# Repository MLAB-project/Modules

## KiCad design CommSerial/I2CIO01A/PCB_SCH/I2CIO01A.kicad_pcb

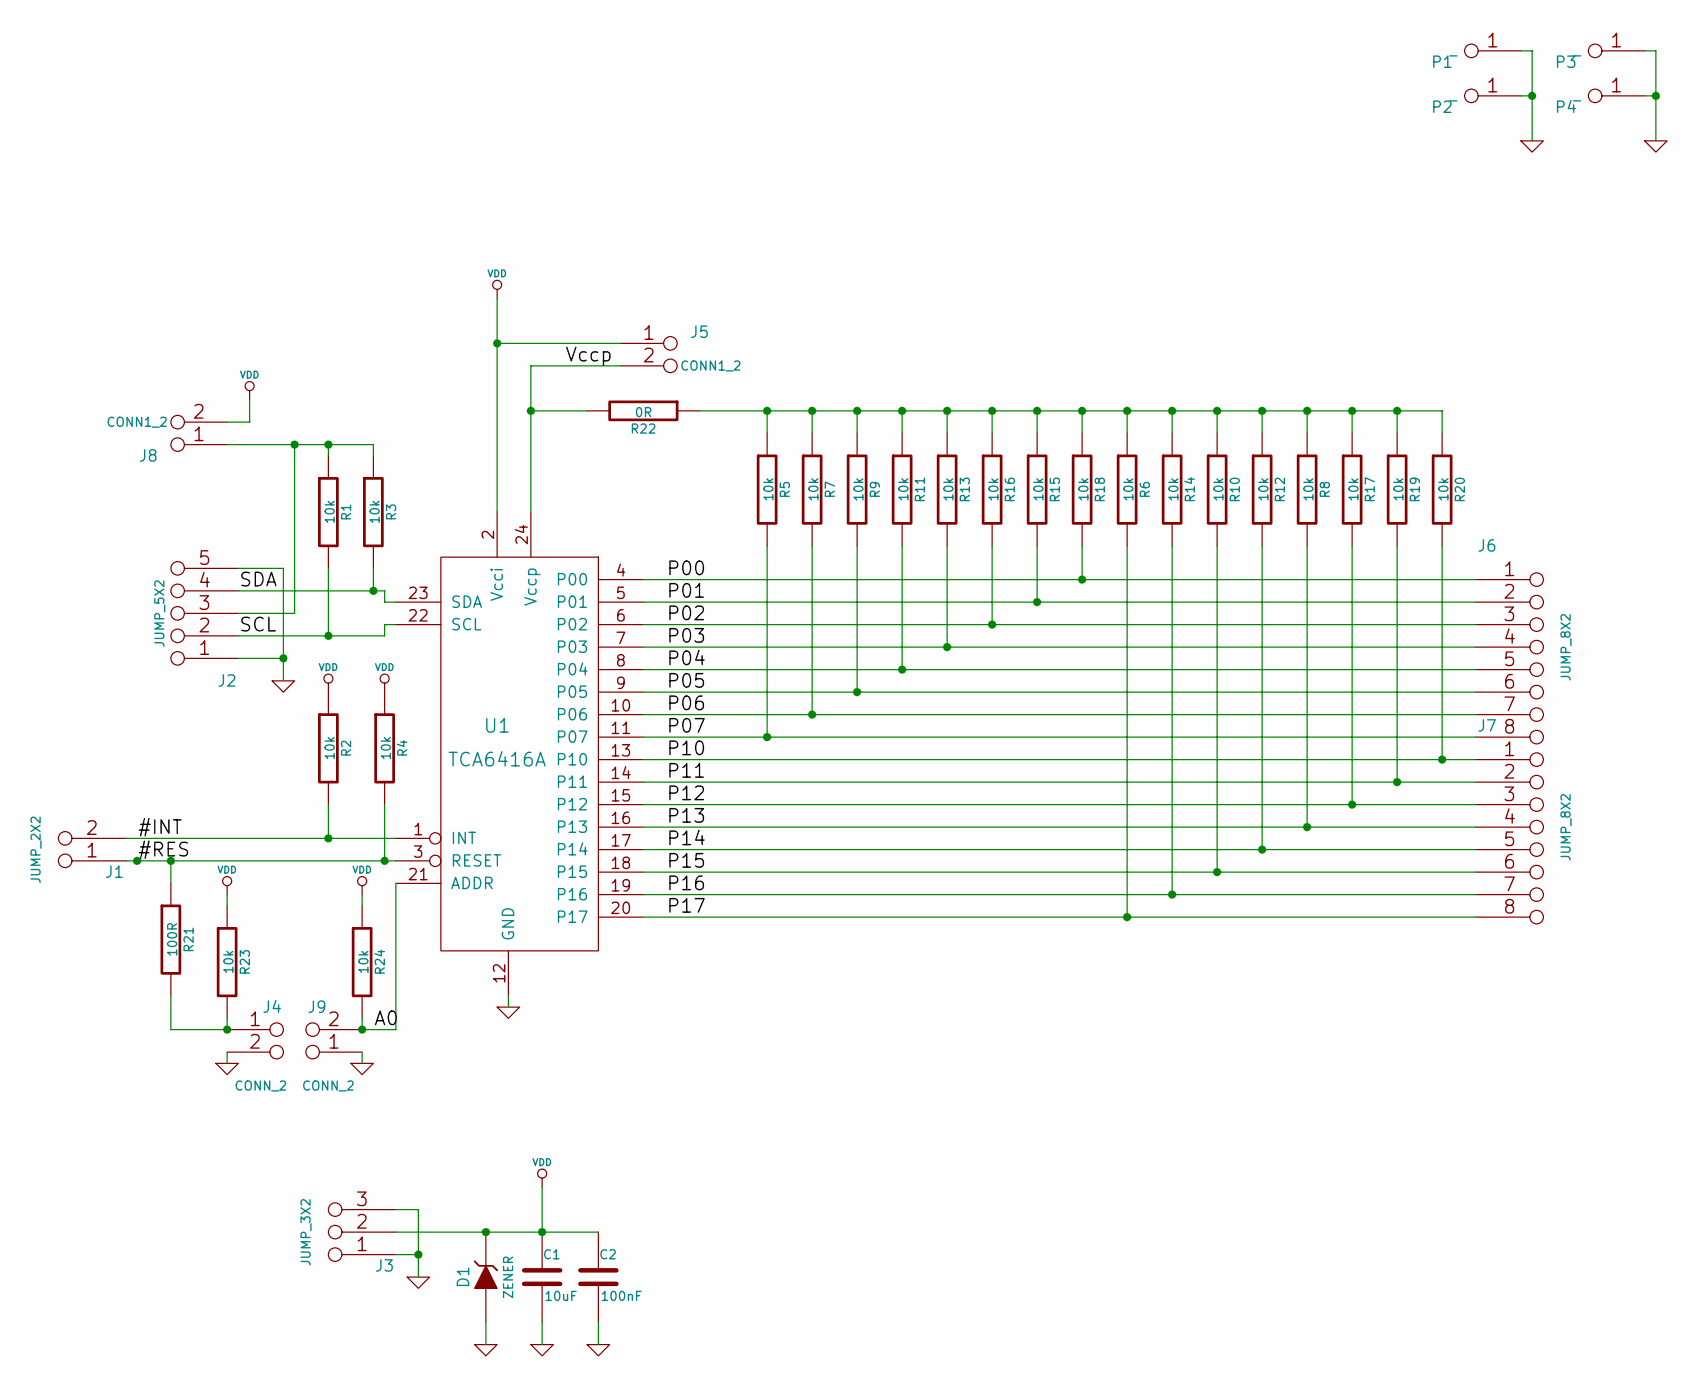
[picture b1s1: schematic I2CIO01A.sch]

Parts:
C1: 10uF; SMD-0805
C2: 100nF; SMD-0805
D1: ZENER; Diode-MiniMELF_Standard
J1: JUMP_2X2; Pin_Header_Straight_2x02
J2: JUMP_5X2; Pin_Header_Straight_2x05
J3: JUMP_3X2; Pin_Header_Straight_2x03
J4, J9: CONN_2; Pin_Header_Straight_1x02
J5, J8: CONN1_2; Pin_Header_Straight_1x02
J6, J7: JUMP_8X2; Pin_Header_Straight_2x08
P1, P2, P3, P4: _; MountingHole_3mm
R1, R2, R3, R4, R5, R6, R7, R8, R9, R10, R11, R12, R13, R14, R15, R16, R17, R18, R19, R20, R23, R24: 10k; SMD-0805
R21: 100R; SMD-0805
R22: 0R; SMD-0805
U1: TCA6416A; TSSOP-28

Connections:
/#INT: J1.2 (1), J1.3, R2.2, U1.1 (INT)
/#RES: J1.1, J1.4, R4.2, R21.1, U1.3 (RESET)
/A0: J9.2 (PM), R24.2, U1.21 (ADDR)
/P00: J6.1, J6.16, R18.2, U1.4 (P00)
/P01: J6.2, J6.15, R15.2, U1.5 (P01)
/P02: J6.3, J6.14, R16.2, U1.6 (P02)
/P03: J6.4, J6.13, R13.2, U1.7 (P03)
/P04: J6.5, J6.12, R11.2, U1.8 (P04)
/P05: J6.6, J6.11, R9.2, U1.9 (P05)
/P06: J6.7, J6.10, R7.2, U1.10 (P06)
/P07: J6.8, J6.9, R5.2, U1.11 (P07)
/P10: J7.1, J7.16, R20.2, U1.13 (P10)
/P11: J7.2, J7.15, R19.2, U1.14 (P11)
/P12: J7.3, J7.14, R17.2, U1.15 (P12)
/P13: J7.4, J7.13, R8.2, U1.16 (P13)
/P14: J7.5, J7.12, R12.2, U1.17 (P14)
/P15: J7.6, J7.11, R10.2, U1.18 (P15)
/P16: J7.7, J7.10, R14.2, U1.19 (P16)
/P17: J7.8, J7.9, R6.2, U1.20 (P17)
/SCL: J2.2, J2.9, R1.2, U1.22 (SCL)
/SDA: J2.4, J2.7, R3.2, U1.23 (SDA)
/Vccp: J5.2 (PM), R22.2, U1.24 (Vccp)
GND: C1.2, C2.2, D1.1 (A), J2.1, J2.5, J2.6, J2.10, J3.1, J3.3, J3.4, J3.6, J4.2 (PM), J9.1, P1.1, P2.1, P3.1, P4.1, U1.12 (GND)
unnamed: J2.3, J2.8, J8.1, R1.1, R3.1
unnamed: J4.1, R21.2, R23.2
unnamed: R5.1, R6.1, R7.1, R8.1, R9.1, R10.1, R11.1, R12.1, R13.1, R14.1, R15.1, R16.1, R17.1, R18.1, R19.1, R20.1, R22.1
VDD: C1.1, C2.1, D1.2 (K), J3.2 (1), J3.5, J5.1, J8.2 (PM), R2.1, R4.1, R23.1, R24.1, U1.2 (Vcci)

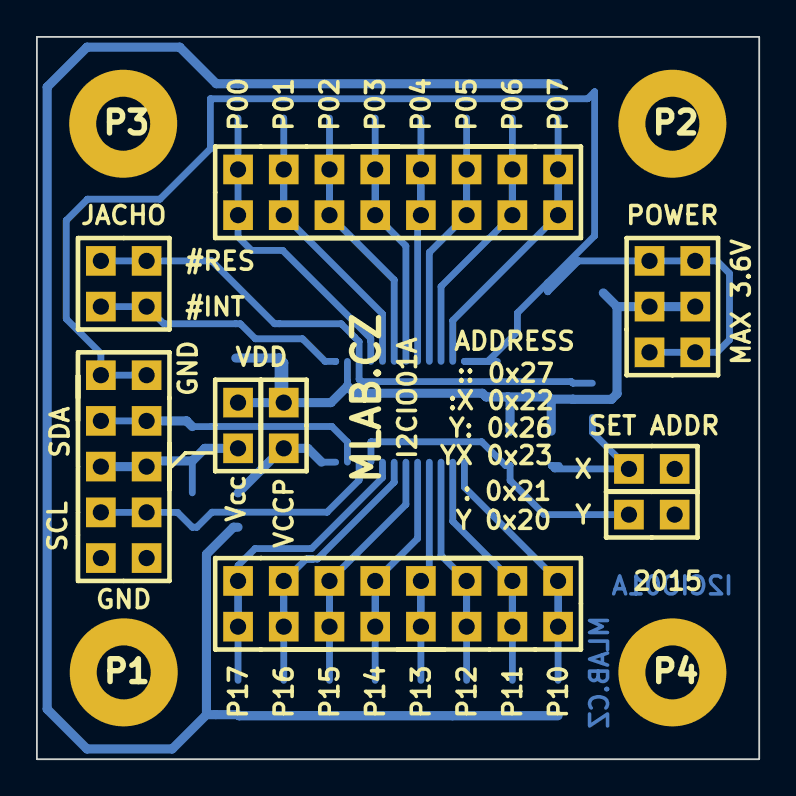
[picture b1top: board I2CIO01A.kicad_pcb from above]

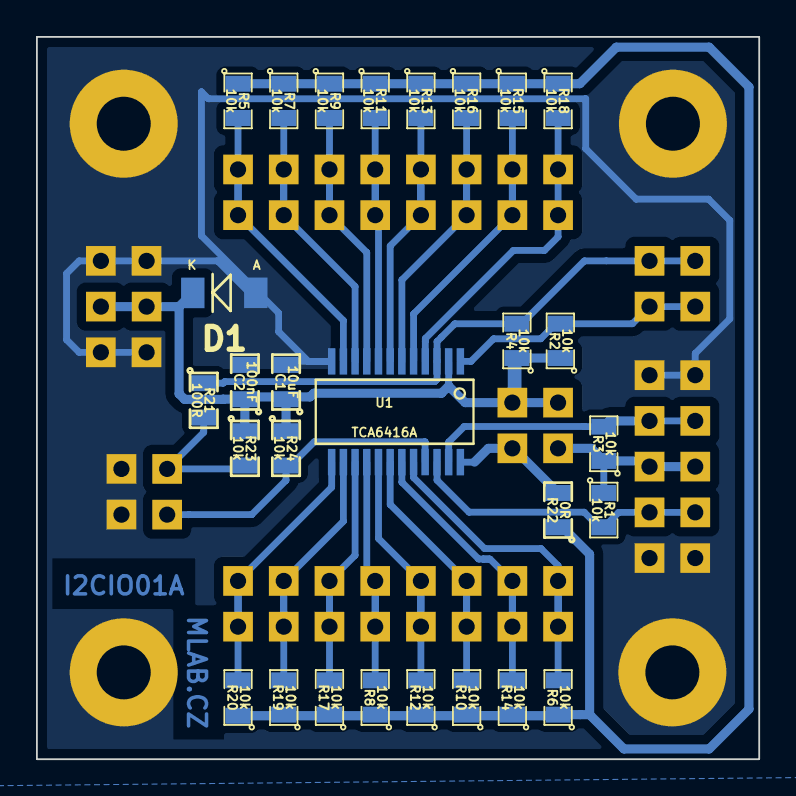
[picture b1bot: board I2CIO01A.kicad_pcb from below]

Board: 2 copper layers, 40.1 x 40.1 mm, 41 parts (28 on the bottom side), 27 nets.

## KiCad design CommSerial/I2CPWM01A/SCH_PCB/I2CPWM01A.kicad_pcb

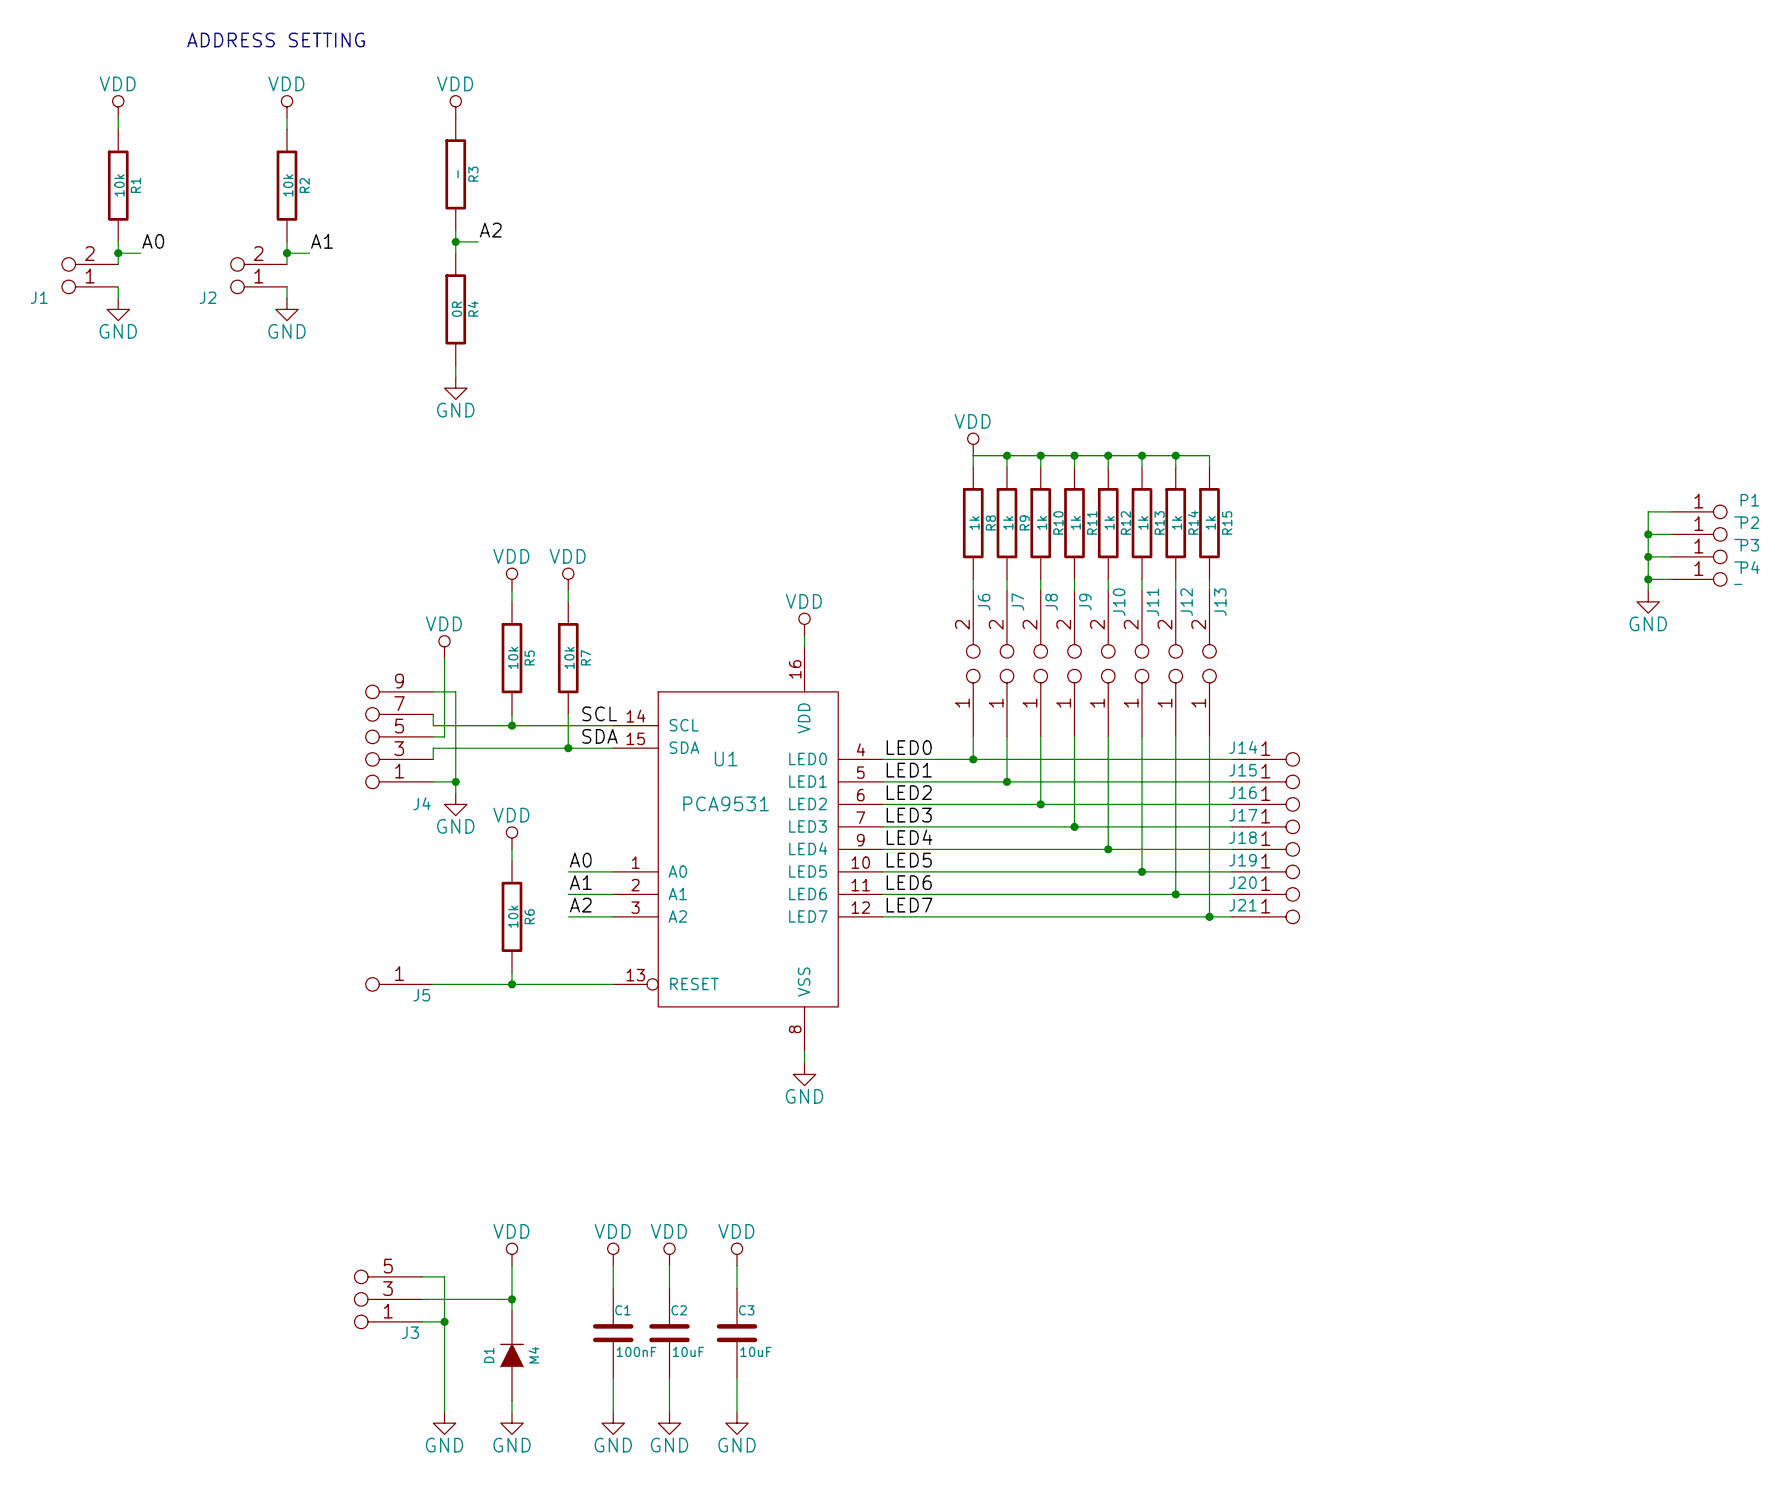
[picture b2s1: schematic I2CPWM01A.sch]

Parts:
C1: 100nF; SMD-0805
C2, C3: 10uF; SMD-0805
D1: M4; SMA_Standard
J1, J2: CONN1_2; Straight_2x01
J3: JUMP_3X2; Straight_2x03
J4: JUMP_5X2; Straight_2x05
J5, J14, J15, J16, J17, J18, J19, J20, J21: JUMP_2x1; Straight_2x01
J6, J7, J8, J9, J10, J11, J12, J13: JUMP2_2x1; Straight_2x01
P1, P2, P3, P4: _; MountingHole_3mm
R1, R2, R5, R6, R7: 10k; SMD-0805
R3: -; SMD-0805
R4: 0R; SMD-0805
R8, R9, R10, R11, R12, R13, R14, R15: 1k; SMD-0805
U1: PCA9531; TSSOP-16_4.4x5mm_Pitch0.65mm

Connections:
/A0: J1.2 (PM), R1.2, U1.1 (A0)
/A1: J2.2 (PM), R2.2, U1.2 (A1)
/A2: R3.2, R4.1, U1.3 (A2)
/LED0: J6.1, J14.1, J14.2, U1.4 (LED0)
/LED1: J7.1, J15.1, J15.2, U1.5 (LED1)
/LED2: J8.1, J16.1, J16.2, U1.6 (LED2)
/LED3: J9.1, J17.1, J17.2, U1.7 (LED3)
/LED4: J10.1, J18.1, J18.2, U1.9 (LED4)
/LED5: J11.1, J19.1, J19.2, U1.10 (LED5)
/LED6: J12.1, J20.1, J20.2, U1.11 (LED6)
/LED7: J13.1, J21.1, J21.2, U1.12 (LED7)
/SCL: J4.7, J4.8 (7), R5.2, U1.14 (SCL)
/SDA: J4.3 (4), J4.4, R7.2, U1.15 (SDA)
GND: C1.2, C2.2, C3.2, D1.1 (A), J1.1, J2.1, J3.1 (2), J3.2, J3.5 (6), J3.6, J4.1 (2), J4.2, J4.9 (10), J4.10, P1.1, P2.1, P3.1, P4.1, R4.2, U1.8 (VSS)
unnamed: J5.1, J5.2, R6.2, U1.13 (RESET)
unnamed: J6.2, R8.2
unnamed: J7.2, R9.2
unnamed: J8.2, R10.2
unnamed: J9.2, R11.2
unnamed: J10.2, R12.2
unnamed: J11.2, R13.2
unnamed: J12.2, R14.2
unnamed: J13.2, R15.2
VDD: C1.1, C2.1, C3.1, D1.2 (K), J3.3 (4), J3.4, J4.5 (6), J4.6, R1.1, R2.1, R3.1, R5.1, R6.1, R7.1, R8.1, R9.1, R10.1, R11.1, R12.1, R13.1, R14.1, R15.1, U1.16 (VDD)

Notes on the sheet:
ADDRESS SETTING

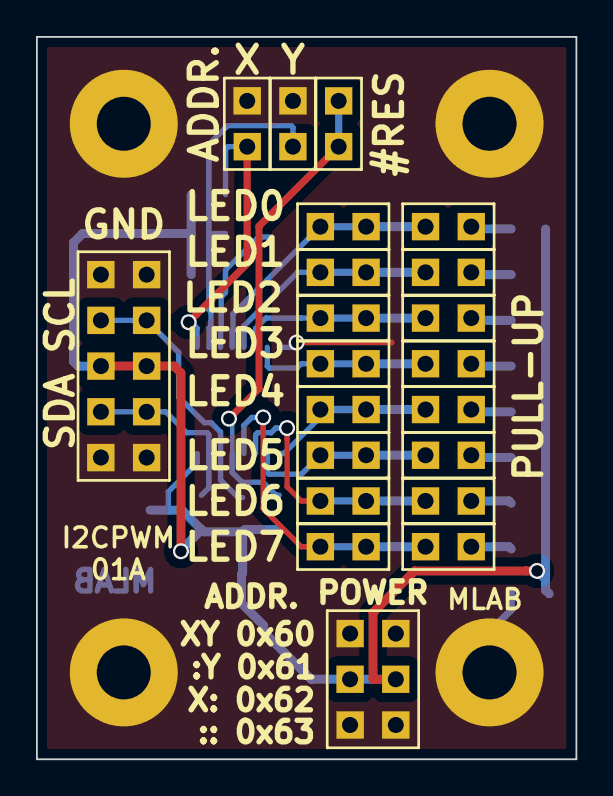
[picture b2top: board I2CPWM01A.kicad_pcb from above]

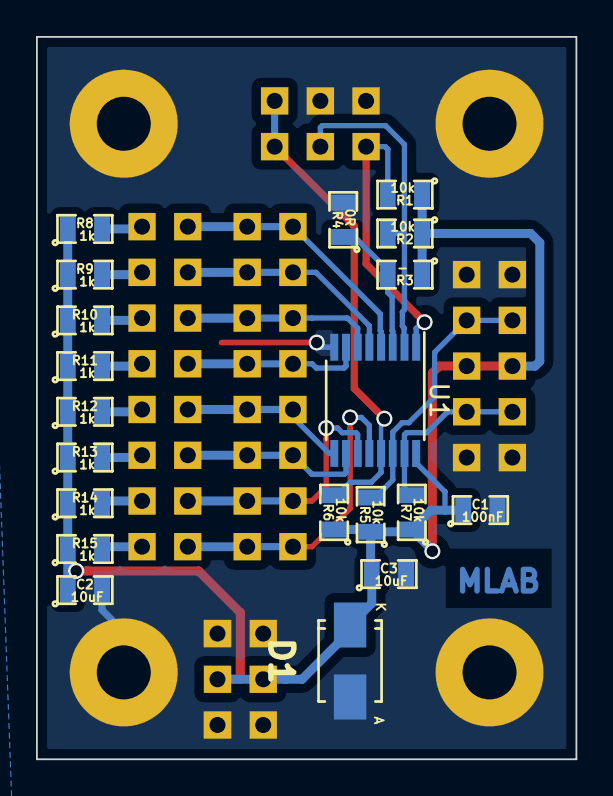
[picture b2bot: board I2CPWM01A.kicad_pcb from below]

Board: 2 copper layers, 30.0 x 40.1 mm, 45 parts (20 on the bottom side), 24 nets.

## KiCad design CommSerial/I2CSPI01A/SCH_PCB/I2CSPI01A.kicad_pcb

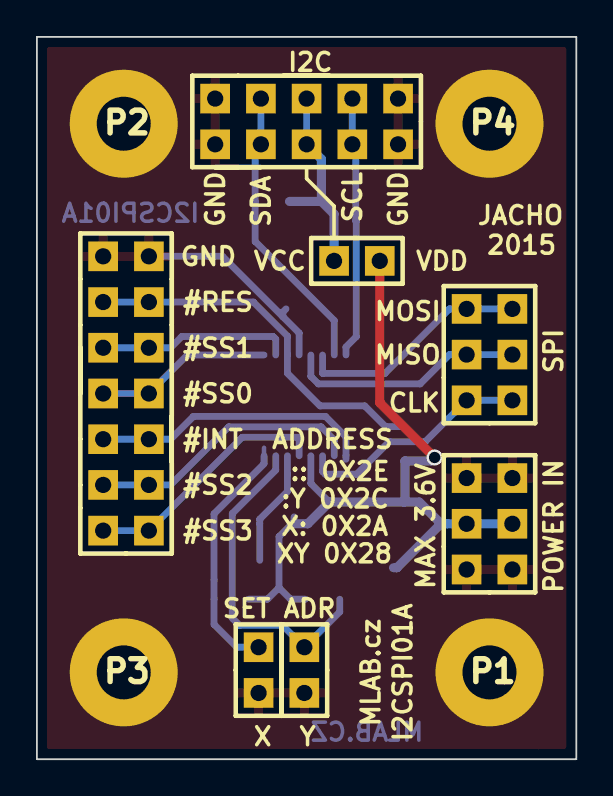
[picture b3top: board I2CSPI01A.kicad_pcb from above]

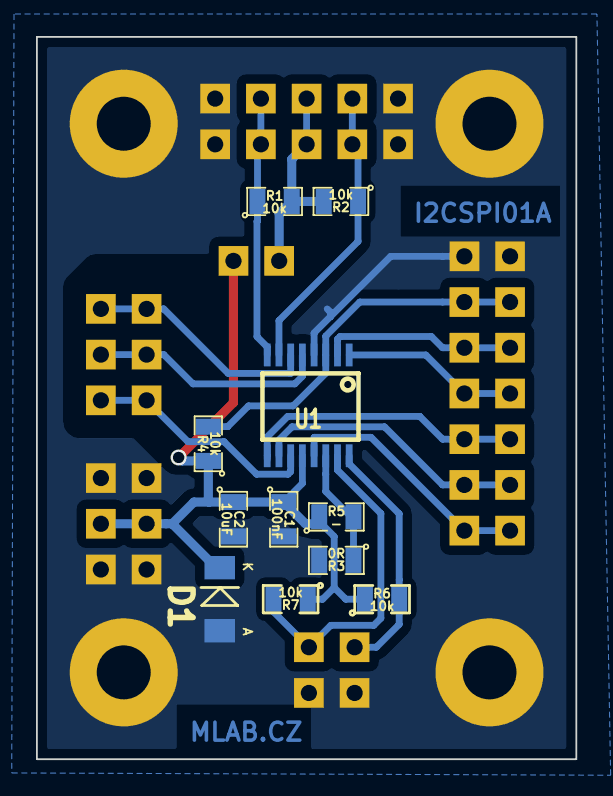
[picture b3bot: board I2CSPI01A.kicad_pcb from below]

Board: 2 copper layers, 30.0 x 40.1 mm, 22 parts (11 on the bottom side), 17 nets.

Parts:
C1: 100nF; SMD-0805
C2: 10uF; SMD-0805
D1: BZV55C-3,6V; Diode-MiniMELF_Standard
J1, J4: JUMP_3X2; Pin_Header_Straight_2x03
J2: JUMP_5X2; Pin_Header_Straight_2x05
J3: JUMP_7X2; Pin_Header_Straight_2x07
J5, J6, J7: CONN_2; Pin_Header_Straight_1x02
P1, P2, P3, P4: _; MountingHole_3mm
R1, R2, R4, R6, R7: 10k; SMD-0805
R3: 0R; SMD-0805
R5: -; SMD-0805
U1: SC18IS602B; TSSOP-16

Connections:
/#INT: J3.3, J3.12, U1.9
/#RES: J3.6, J3.9, R4.2, U1.3
/#SS0: J3.4, J3.11, U1.1
/#SS1: J3.5, J3.10, U1.2
/#SS2: J3.2, J3.13, U1.10
/#SS3: J3.1, J3.14, U1.13
/A0: R3.1, R5.2, U1.14
/A1: J7.2, R7.2, U1.15
/A2: J6.1, R6.2, U1.16
/MISO: J1.2, J1.5, U1.5
/MOSI: J1.3, J1.4, U1.6
/SCL: J2.2, J2.9, R1.1, U1.8
/SDA: J2.4, J2.7, R2.1, U1.7
/SPICLK: J1.1, J1.6, U1.11
GND: C1.2, C2.2, D1.1, J2.1, J2.5, J2.6, J2.10, J3.7, J3.8, J4.1, J4.3, J4.4, J4.6, J6.2, J7.1, P1.1, P2.1, P3.1, P4.1, R3.2, U1.4
unnamed: J2.3, J2.8, J5.1, R1.2, R2.2
VDD: C1.1, C2.1, D1.2, J4.2, J4.5, J5.2, R4.1, R5.1, R6.1, R7.1, U1.12

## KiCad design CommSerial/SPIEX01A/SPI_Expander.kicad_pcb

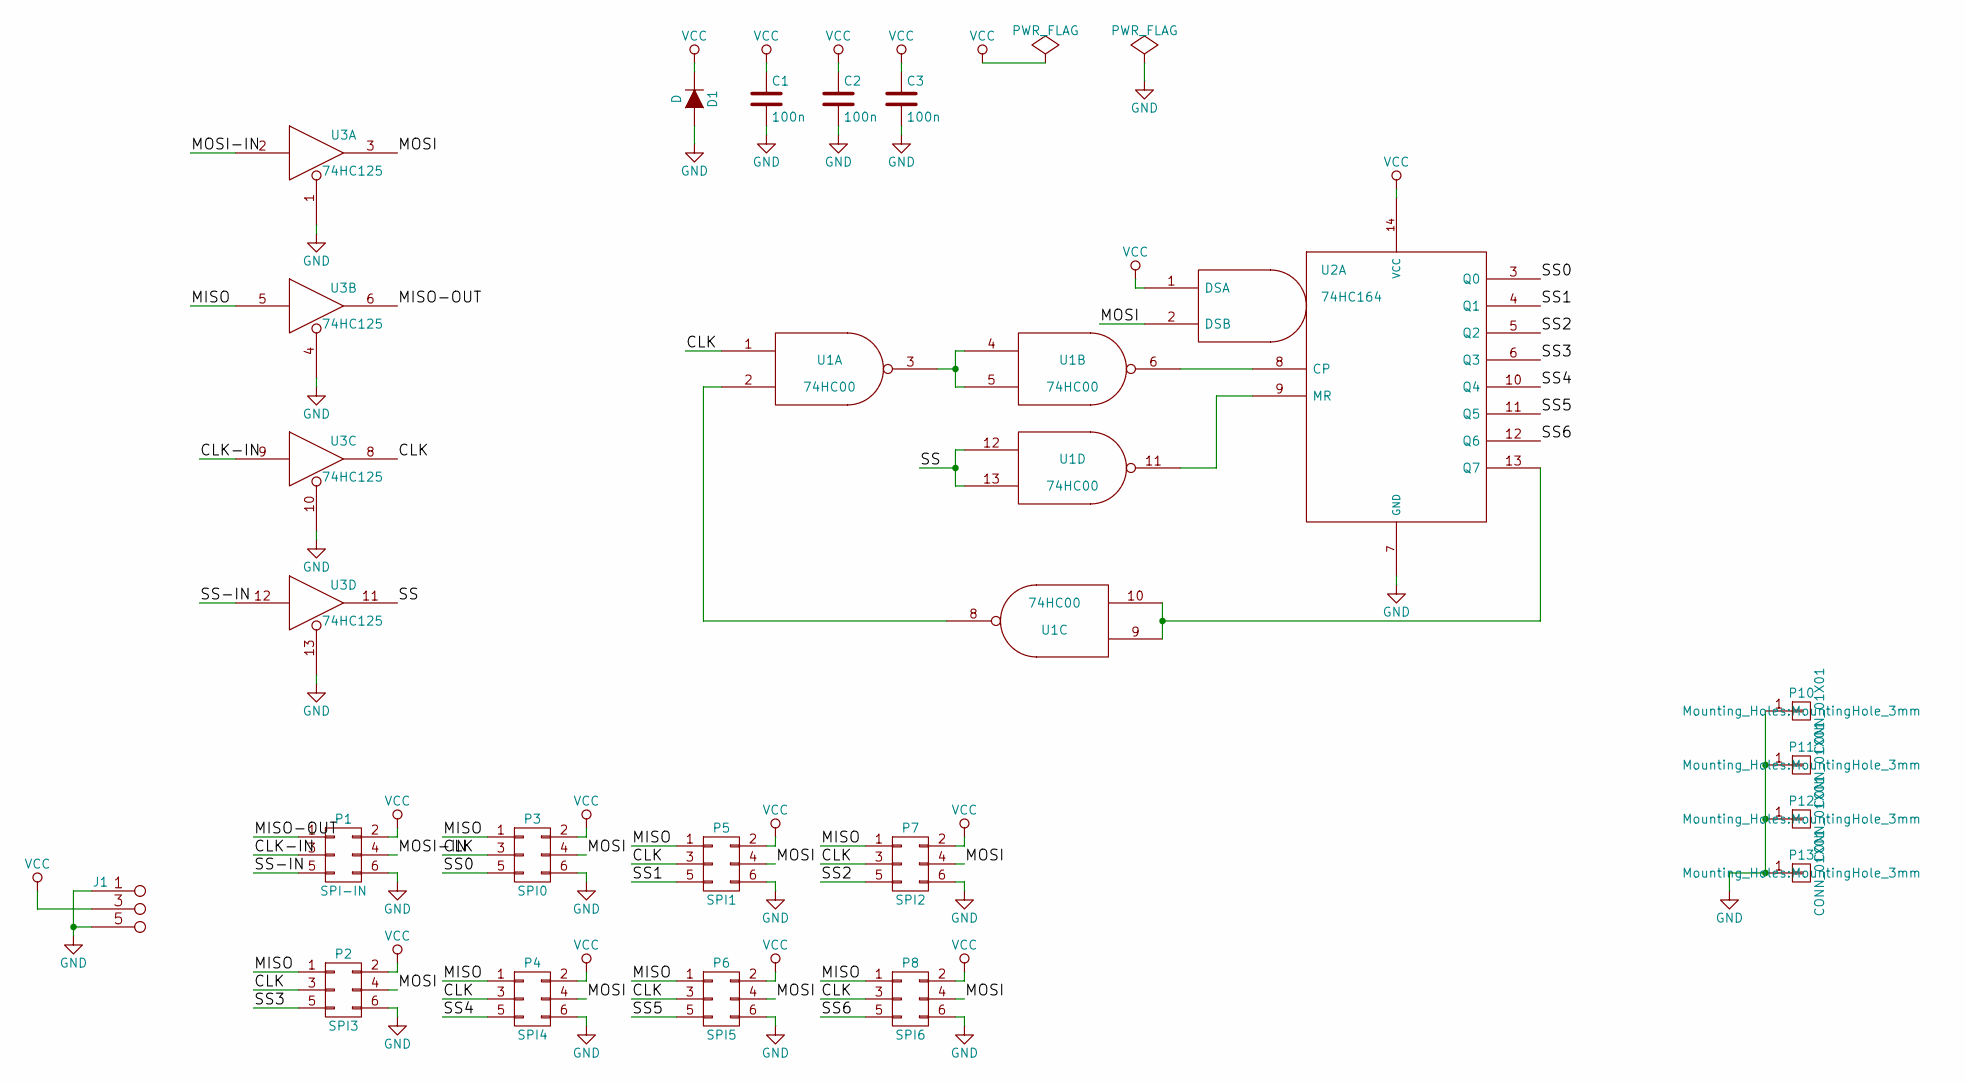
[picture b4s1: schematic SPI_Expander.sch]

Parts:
C1, C2, C3: 100n; C_0603_HandSoldering
D1: D; R_0805_HandSoldering
J1: PWR; Straight_2x03
P1: SPI-IN; Straight_2x03
P2: SPI3; Straight_2x03
P3: SPI0; Straight_2x03
P4: SPI4; Straight_2x03
P5: SPI1; Straight_2x03
P6: SPI5; Straight_2x03
P7: SPI2; Straight_2x03
P8: SPI6; Straight_2x03
P10, P11, P12, P13: CONN_01X01; MountingHole_3mm
U1: 74HC00; SOIC-14_3.9x8.7mm_Pitch1.27mm
U2: 74HC164; SOIC-14_3.9x8.7mm_Pitch1.27mm
U3: 74HC125; SOIC-14_3.9x8.7mm_Pitch1.27mm

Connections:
/CLK: P2.3, P3.3, P4.3, P5.3, P6.3, P7.3, P8.3, U1.1, U3.8
/CLK-IN: P1.3, U3.9
/MISO: P2.1, P3.1, P4.1, P5.1, P6.1, P7.1, P8.1, U3.5
/MISO-OUT: P1.1, U3.6
/MOSI: P2.4, P3.4, P4.4, P5.4, P6.4, P7.4, P8.4, U2.2 (DSB), U3.3
/MOSI-IN: P1.4, U3.2
/SS: U1.12, U1.13, U3.11
/SS0: P3.5, U2.3 (Q0)
/SS1: P5.5, U2.4 (Q1)
/SS2: P7.5, U2.5 (Q2)
/SS3: P2.5, U2.6 (Q3)
/SS4: P4.5, U2.10 (Q4)
/SS5: P6.5, U2.11 (Q5)
/SS6: P8.5, U2.12 (Q6)
/SS-IN: P1.5, U3.12
GND: C1.2, C2.2, C3.2, D1.2 (A), J1.1 (2), J1.2, J1.5 (6), J1.6, P1.6, P2.6, P3.6, P4.6, P5.6, P6.6, P7.6, P8.6, P10.1, P11.1, P12.1, P13.1, U1.7 (GND), U2.7 (GND), U3.1, U3.4, U3.7 (GND), U3.10, U3.13
unnamed: U1.2, U1.8
unnamed: U1.3, U1.4, U1.5
unnamed: U1.6, U2.8 (CP)
unnamed: U1.9, U1.10, U2.13 (Q7)
unnamed: U1.11, U2.9 (MR)
VCC: C1.1, C2.1, C3.1, D1.1 (K), J1.3 (4), J1.4, P1.2, P2.2, P3.2, P4.2, P5.2, P6.2, P7.2, P8.2, U1.14 (VCC), U2.1 (DSA), U2.14 (VCC), U3.14 (VCC)

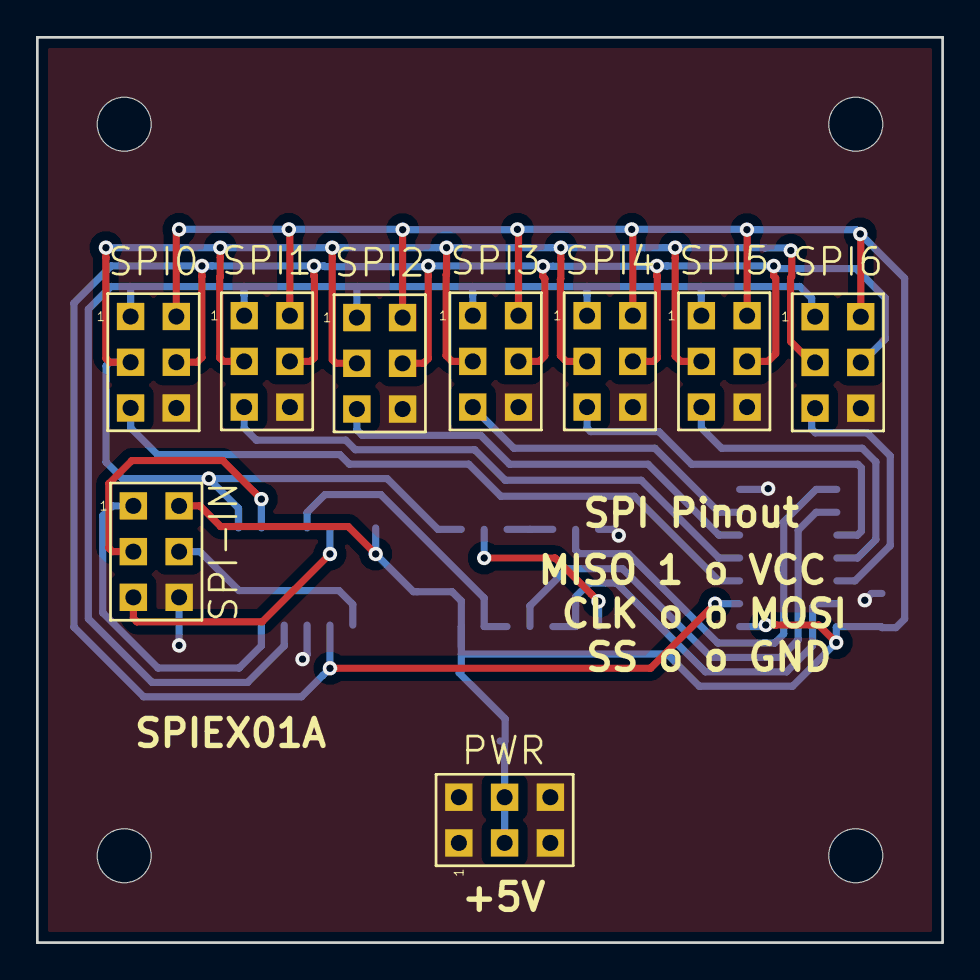
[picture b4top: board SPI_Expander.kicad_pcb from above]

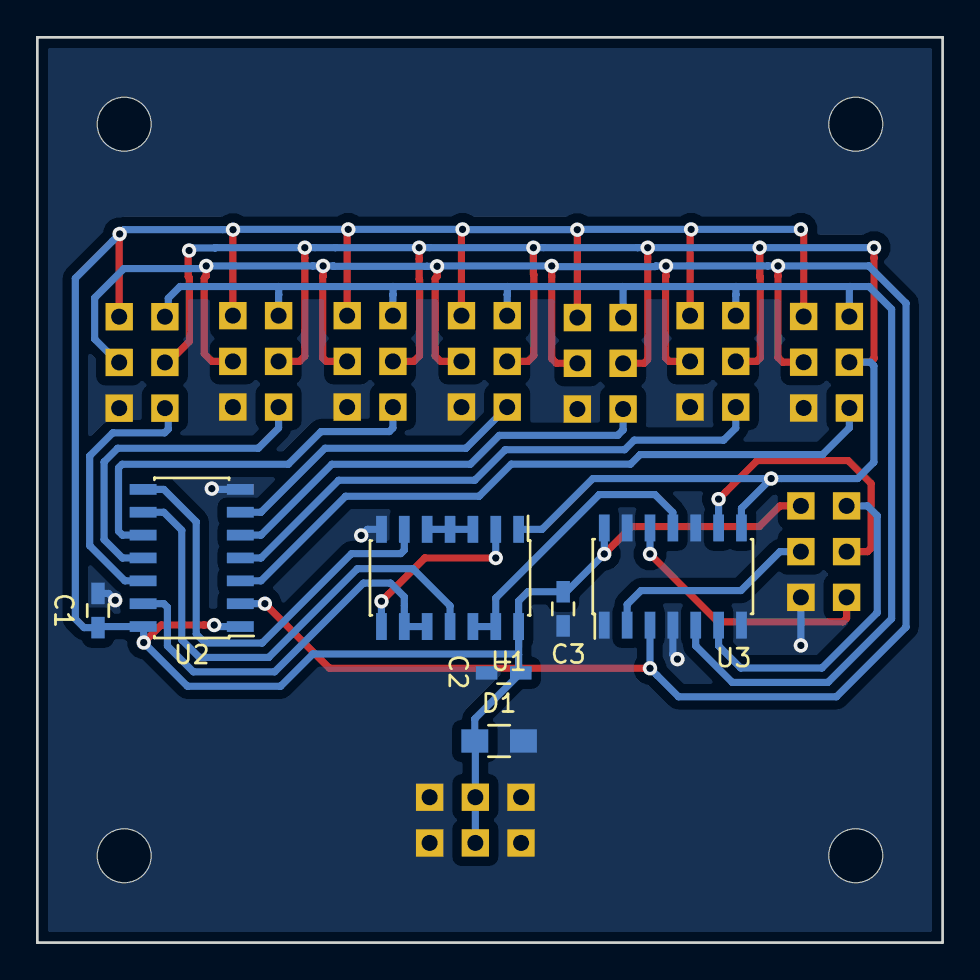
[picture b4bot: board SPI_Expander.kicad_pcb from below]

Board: 2 copper layers, 50.3 x 50.3 mm, 20 parts (11 on the bottom side), 22 nets.

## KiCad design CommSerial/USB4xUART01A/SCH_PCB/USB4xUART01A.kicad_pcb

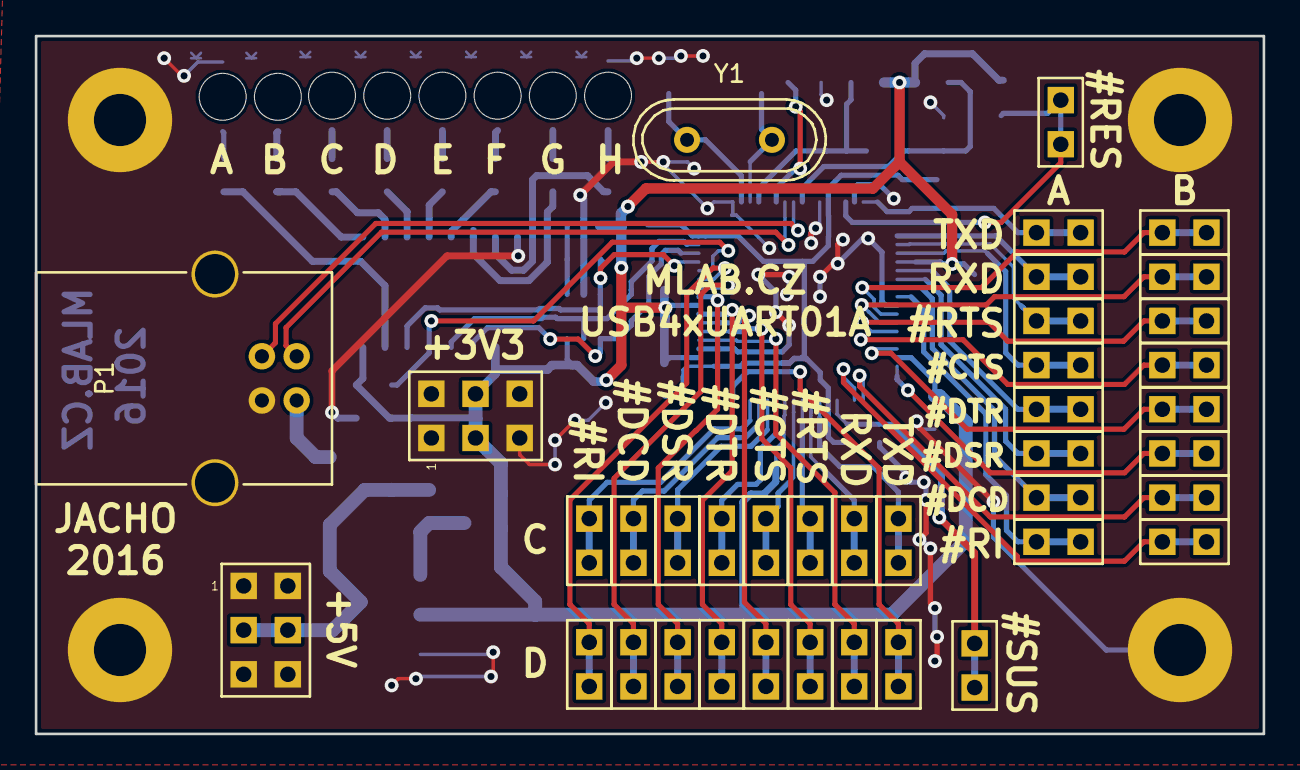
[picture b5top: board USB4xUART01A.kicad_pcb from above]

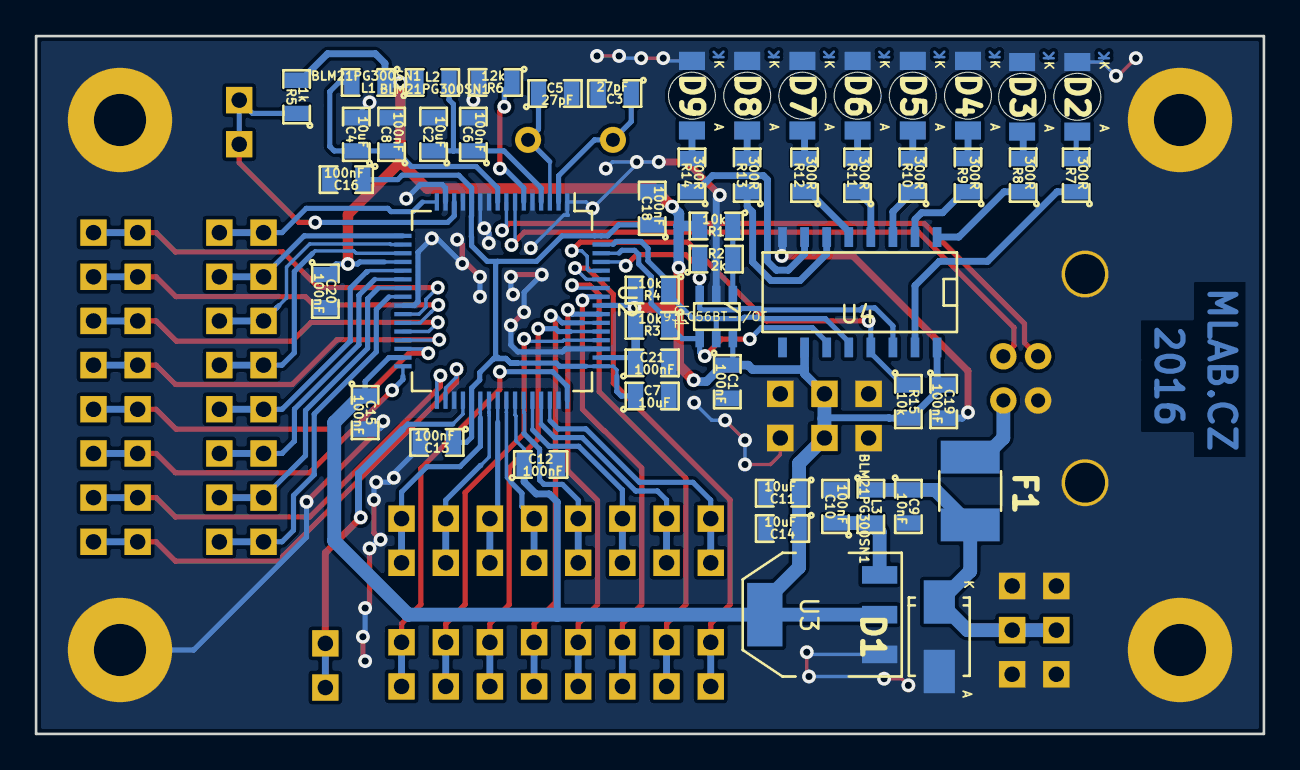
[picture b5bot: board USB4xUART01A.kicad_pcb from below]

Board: 2 copper layers, 70.6 x 40.1 mm, 94 parts (52 on the bottom side), 68 nets.

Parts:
C1, C6, C8, C10, C12, C13, C15, C16, C18, C19, C20, C21: 100nF; SMD-0805
C2, C4, C7, C11, C14: 10uF; SMD-0805
C3, C5: 27pF; SMD-0805
C9: 10nF; SMD-0805
D1: M4; Diode-SMA_Standard
D2, D3, D4, D5, D6, D7, D8, D9: RED; LED_1206
F1: 750mA; 1812
J1, J2, J3, J4, J5, J6, J7, J8, J9, J10, J11, J12, J13, J14, J15, J16, J17, J18, J19, J20, J21, J22, J23, J24, J25, J26, J27, J28, J29, J30, J31, J32, J33, J34: JUMP_2x1; Straight_1x02
J35, J36: JUMP_3X2; Straight_2x03
L1, L2, L3: BLM21PG300SN1; SMD-0805
M1, M2, M3, M4: HOLE; MountingHole_3mm
P1: USB_B
R1, R3, R4, R15: 10k; SMD-0805
R2: 2k; SMD-0805
R5: 1k; SMD-0805
R6: 12k; SMD-0805
R7, R8, R9, R10, R11, R12, R13, R14: 300R; SMD-0805
U1: 93LC56BT-I/OT; SOT-23-6
U2: FT4232HL; LQFP-64_10x10mm_Pitch0.5mm
U3: LM1117_3V3; SOT-223
U4: SN74HC595D; SO-16-N
Y1: 12MHz; Crystal_HC49-U_Vertical

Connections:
+1V8: C7.1, C13.1, C16.1, C18.1, U2.12, U2.37, U2.49, U2.64
+3V3: C1.1, C11.1, C12.1, C14.1, C15.1, C19.1, C20.1, C21.1, J36.3, J36.4, L1.1, L2.1, R1.2, R3.2, R4.2, R5.2, R15.2, U1.6, U2.20, U2.31, U2.42, U2.50, U2.56, U3.2, U3.4, U4.10, U4.16
+5V: C9.1, D1.1, F1.2, J35.3, J35.4, L3.1
/#PWREN: R15.1, U2.60, U4.13
/A: R7.1, U4.15
/A_CTS: J5.1, J5.2, U2.19
/A_DCD: J8.1, J8.2, U2.23
/A_DSR: J7.1, J7.2, U2.22
/A_DTR: J6.1, J6.2, U2.21
/A_RI: J9.1, J9.2, U2.24
/A_RTS: J4.1, J4.2, U2.18
/A_RXD: J3.1, J3.2, U2.17
/A_TXD: J2.1, J2.2, U2.16
/B: R8.1, U4.1
/B_CTS: J13.1, J13.2, U2.29
/B_DCD: J16.1, J16.2, U2.33
/B_DSR: J15.1, J15.2, U2.32
/B_DTR: J14.1, J14.2, U2.30
/B_RI: J17.1, J17.2, U2.34
/B_RTS: J12.1, J12.2, U2.28
/B_RXD: J11.1, J11.2, U2.27
/B_TXD: J10.1, J10.2, U2.26
/C: R9.1, U4.2
/C_CTS: J21.1, J21.2, U2.41
/C_DCD: J24.1, J24.2, U2.45
/C_DSR: J23.1, J23.2, U2.44
/C_DTR: J22.1, J22.2, U2.43
/C_RI: J25.1, J25.2, U2.46
/C_RTS: J20.1, J20.2, U2.40
/C_RXD: J19.1, J19.2, U2.39
/C_TXD: J18.1, J18.2, U2.38
/D: R10.1, U4.3
/D+: P1.3, U2.8
/D-: P1.2, U2.7
/D_CTS: J29.1, J29.2, U2.54
/D_DCD: J32.1, J32.2, U2.58
/D_DSR: J31.1, J31.2, U2.57
/D_DTR: J30.1, J30.2, U2.55
/D_RI: J33.1, J33.2, U2.59
/D_RTS: J28.1, J28.2, U2.53
/D_RXD: J27.1, J27.2, U2.52
/D_TXD: J26.1, J26.2, U2.48
/E: R11.1, U4.4
/EECLK: R3.1, U1.4, U2.62, U4.11
/EECS: R4.1, U1.5, U2.63, U4.12
/EEDATA: R2.1, U1.3, U2.61, U4.14
/F: R12.1, U4.5
/G: R13.1, U4.6
/H: R14.1, U4.7
/RES: J1.1, J1.2, R5.1, U2.14
/SUSPEND: J34.1, J34.2, U2.36
GND: C1.2, C2.2, C3.2, C4.2, C5.2, C6.2, C7.2, C8.2, C9.2, C10.2, C11.2, C12.2, C13.2, C14.2, C15.2, C16.2, C18.2, C19.2, C20.2, C21.2, D1.2, D2.1, D3.1, D4.1, D5.1, D6.1, D7.1, D8.1, D9.1, J35.1, J35.2, J35.5, J35.6, J36.1, J36.2, J36.5, J36.6, M1.1, M2.1, M3.1, M4.1, P1.4, P1.5, R6.2, U1.2, U2.1, U2.5, U2.10, U2.11, U2.13, U2.15, U2.25, U2.35, U2.47, U2.51, U3.1, U4.8
unnamed: C2.1, C6.1, L2.2, U2.4
unnamed: C3.1, U2.2, Y1.1
unnamed: C4.1, C8.1, L1.2, U2.9
unnamed: C5.1, U2.3, Y1.2
unnamed: C10.1, L3.2, U3.3
unnamed: D2.2, R7.2
unnamed: D3.2, R8.2
unnamed: D4.2, R9.2
unnamed: D5.2, R10.2
unnamed: D6.2, R11.2
unnamed: D7.2, R12.2
unnamed: D8.2, R13.2
unnamed: D9.2, R14.2
unnamed: F1.1, P1.1
unnamed: R1.1, R2.2, U1.1
unnamed: R6.1, U2.6
